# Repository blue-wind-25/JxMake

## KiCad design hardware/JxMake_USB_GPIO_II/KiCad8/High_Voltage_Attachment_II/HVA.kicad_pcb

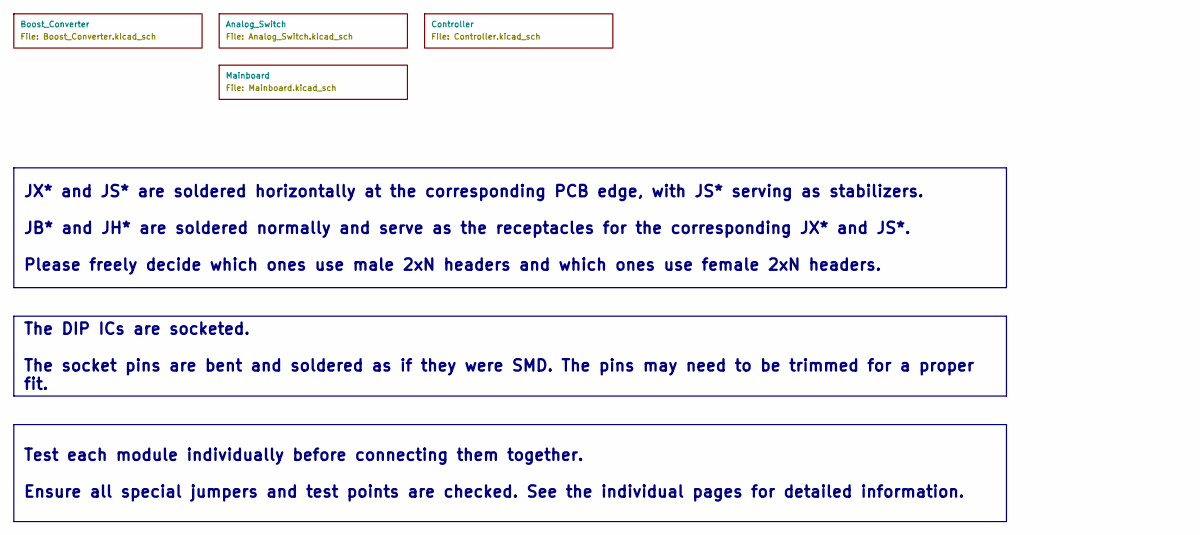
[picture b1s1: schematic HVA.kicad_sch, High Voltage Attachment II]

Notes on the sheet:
Test each module individually before connecting them together. Ensure all special jumpers and test points are checked. See the individual pages for detailed information.
The DIP ICs are socketed. The socket pins are bent and soldered as if they were SMD. The pins may need to be trimmed for a proper fit.
JX* and JS* are soldered horizontally at the corresponding PCB edge, with JS* serving as stabilizers. JB* and JH* are soldered normally and serve as the receptacles for the corresponding JX* and JS*. Please freely decide which ones use male 2xN headers and which ones use female 2xN headers.

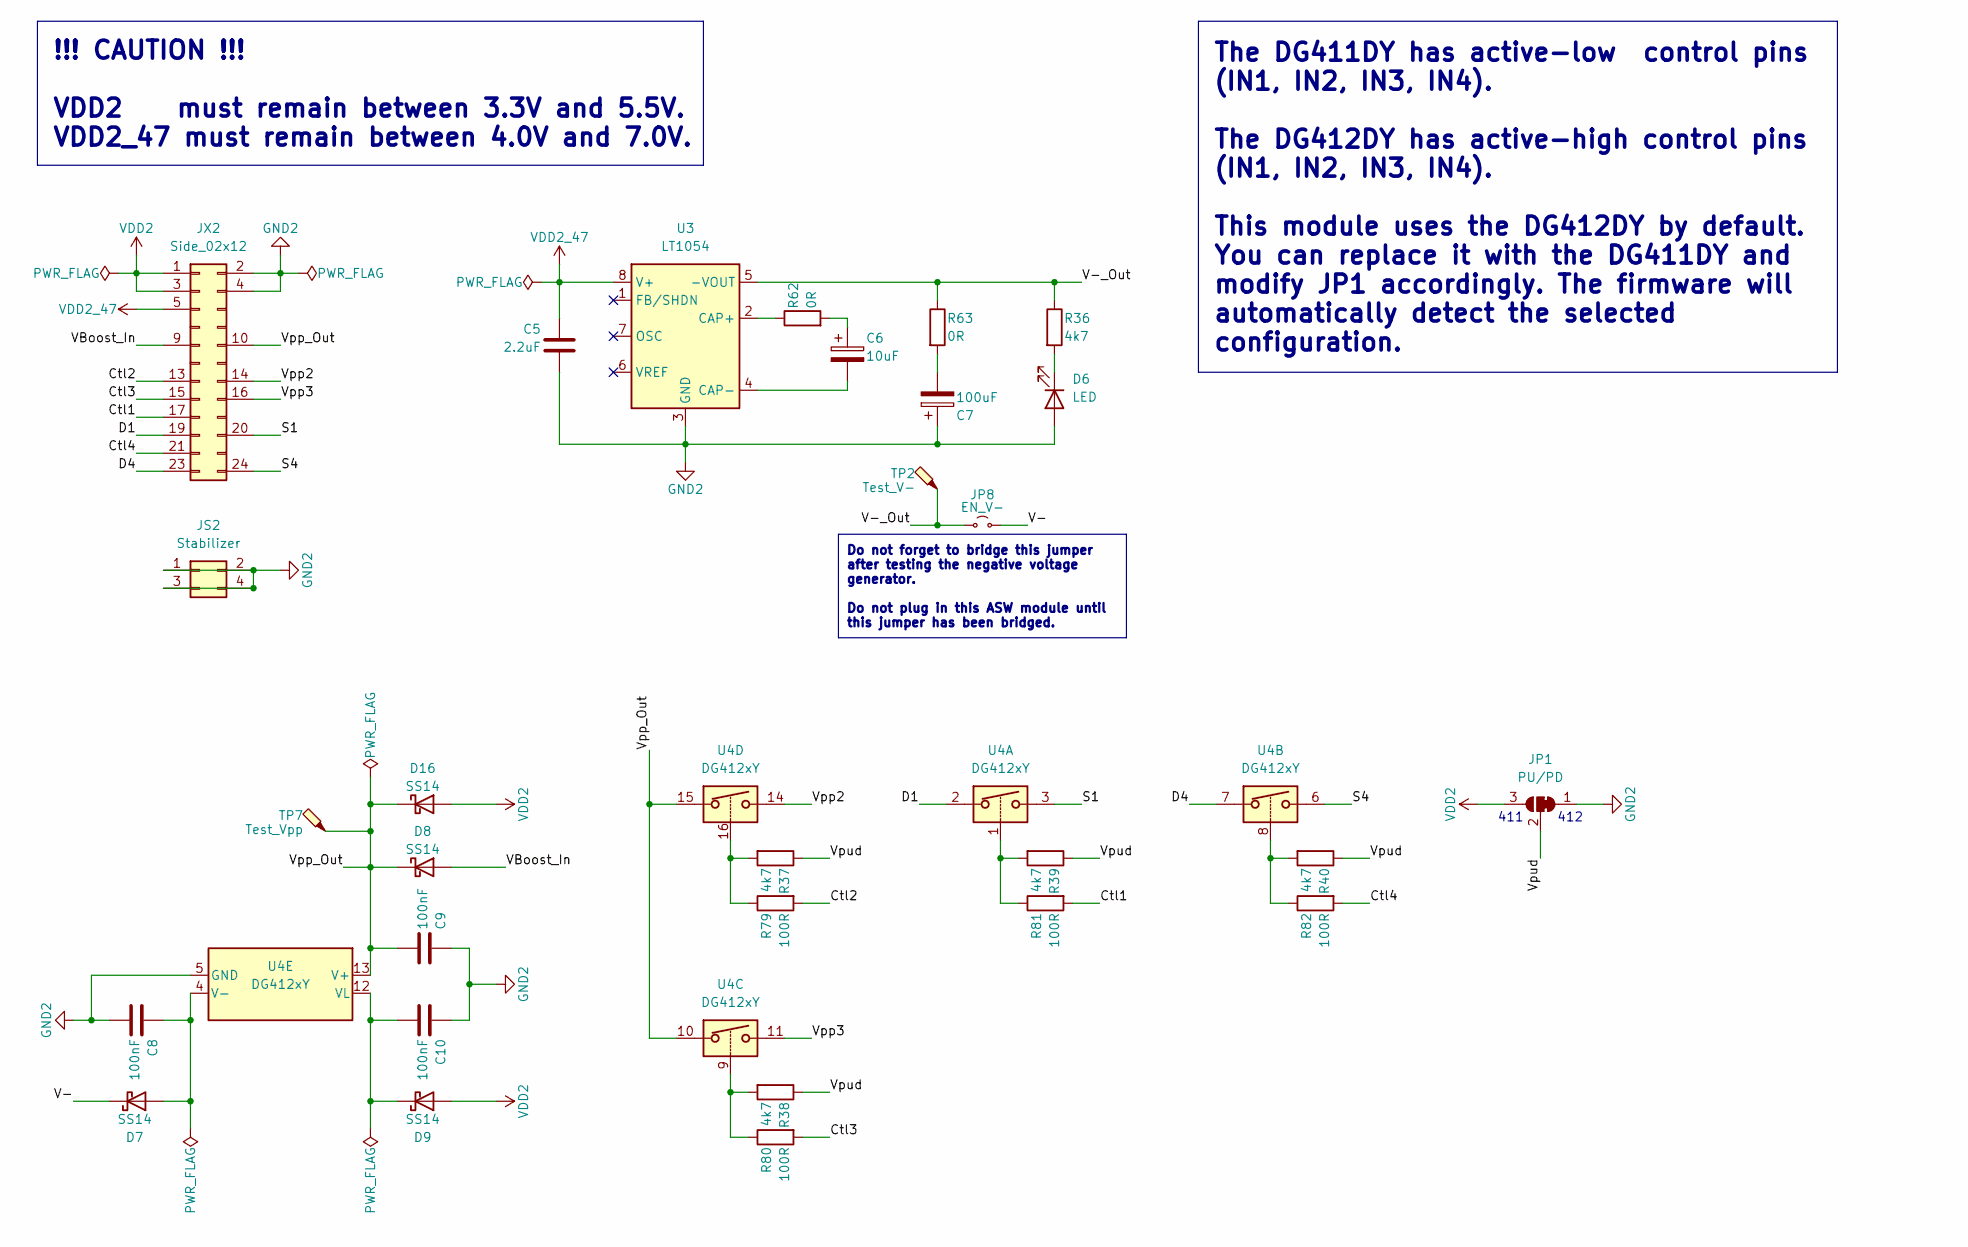
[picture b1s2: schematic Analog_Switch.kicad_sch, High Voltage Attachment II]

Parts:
C5: 2.2uF; C_0805_2012Metric_Pad1.18x1.45mm_HandSolder
C6: 10uF; CP_EIA-7360-38_Kemet-E_Pad2.25x4.25mm_HandSolder
C7: 100uF; CP_EIA-7360-38_Kemet-E_Pad2.25x4.25mm_HandSolder
C8, C9, C10: 100nF; C_0805_2012Metric_Pad1.18x1.45mm_HandSolder
D6: LED; LED_0805_2012Metric_Pad1.15x1.40mm_HandSolder
D7, D8, D9, D16: SS14; D_SMA
JP1: PU/PD; SolderJumper-3_P1.3mm_Bridged12_RoundedPad1.0x1.5mm
JP8: EN_V-; SolderJumper-2_P1.3mm_Open_RoundedPad1.0x1.5mm
JS2: Stabilizer; PinHeader_2x02_P2.54mm_Vertical
JX2: Side_02x12; PinHeader_2x12_P2.54mm_Vertical
R36, R37, R38, R39, R40: 4k7; R_0805_2012Metric_Pad1.20x1.40mm_HandSolder
R62, R63: 0R; R_0805_2012Metric_Pad1.20x1.40mm_HandSolder
R79, R80, R81, R82: 100R; R_0805_2012Metric_Pad1.20x1.40mm_HandSolder
TP2: Test_V-; TestPoint_THTPad_D1.5mm_Drill0.7mm
TP7: Test_Vpp; TestPoint_THTPad_D1.5mm_Drill0.7mm
U3: LT1054; DIP-8_W7.62mm_LongPads
U4: DG412xY; SOIC-16_3.9x9.9mm_P1.27mm

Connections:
/Analog_Switch/Ctl1: JX2.17, R81.2
/Analog_Switch/Ctl2: JX2.13, R79.2
/Analog_Switch/Ctl3: JX2.15, R80.2
/Analog_Switch/Ctl4: JX2.21, R82.2
/Analog_Switch/D1: JX2.19, U4.2
/Analog_Switch/D4: JX2.23, U4.7
/Analog_Switch/S1: JX2.20, U4.3
/Analog_Switch/S4: JX2.24, U4.6
/Analog_Switch/V-: D7.1 (K), JP8.2 (B)
/Analog_Switch/V-_Out: JP8.1 (A), R36.1, R63.1, TP2.1, U3.5 (-VOUT)
/Analog_Switch/VBoost_In: D8.2 (A), JX2.9
/Analog_Switch/Vpp2: JX2.14, U4.14
/Analog_Switch/Vpp3: JX2.16, U4.11
/Analog_Switch/Vpp_Out: C9.2, D8.1 (K), D16.1 (K), JX2.10, TP7.1, U4.10, U4.13 (V+), U4.15
/Analog_Switch/Vpud: JP1.2 (C), R37.1, R38.1, R39.1, R40.1
GND2: C5.2, C7.1, C8.2, C9.1, C10.1, D6.2 (A), JP1.1 (A), JS2.1, JS2.2, JS2.3, JS2.4, JX2.2, JX2.4, U3.3 (GND), U4.5 (GND)
unnamed: C6.1, R62.2
unnamed: C7.2, R63.2
unnamed: D6.1 (K), R36.2
unnamed: C8.1, D7.2 (A), U4.4 (V-)
unnamed: C10.2, D9.1 (K), U4.12 (VL)
unnamed: R37.2, R79.1, U4.16
unnamed: R38.2, R80.1, U4.9
unnamed: R39.2, R81.1, U4.1
unnamed: R40.2, R82.1, U4.8
unnamed: R62.1, U3.2 (CAP+)
unnamed: C6.2, U3.4 (CAP-)
VDD2: D9.2 (A), D16.2 (A), JP1.3 (B), JX2.1, JX2.3
VDD2_47: C5.1, JX2.5, U3.8 (V+)

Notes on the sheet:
Do not forget to bridge this jumper after testing the negative voltage generator. Do not plug in this ASW module until this jumper has been bridged.
The DG411DY has active-low control pins (IN1, IN2, IN3, IN4). The DG412DY has active-high control pins (IN1, IN2, IN3, IN4). This module uses the DG412DY by default. You can replace it with the DG411DY and modify JP1 accordingly. The firmware will automatically detect the selected configuration.
!!! CAUTION !!! VDD2 must remain between 3.3V and 5.5V. VDD2_47 must remain between 4.0V and 7.0V.
411
412

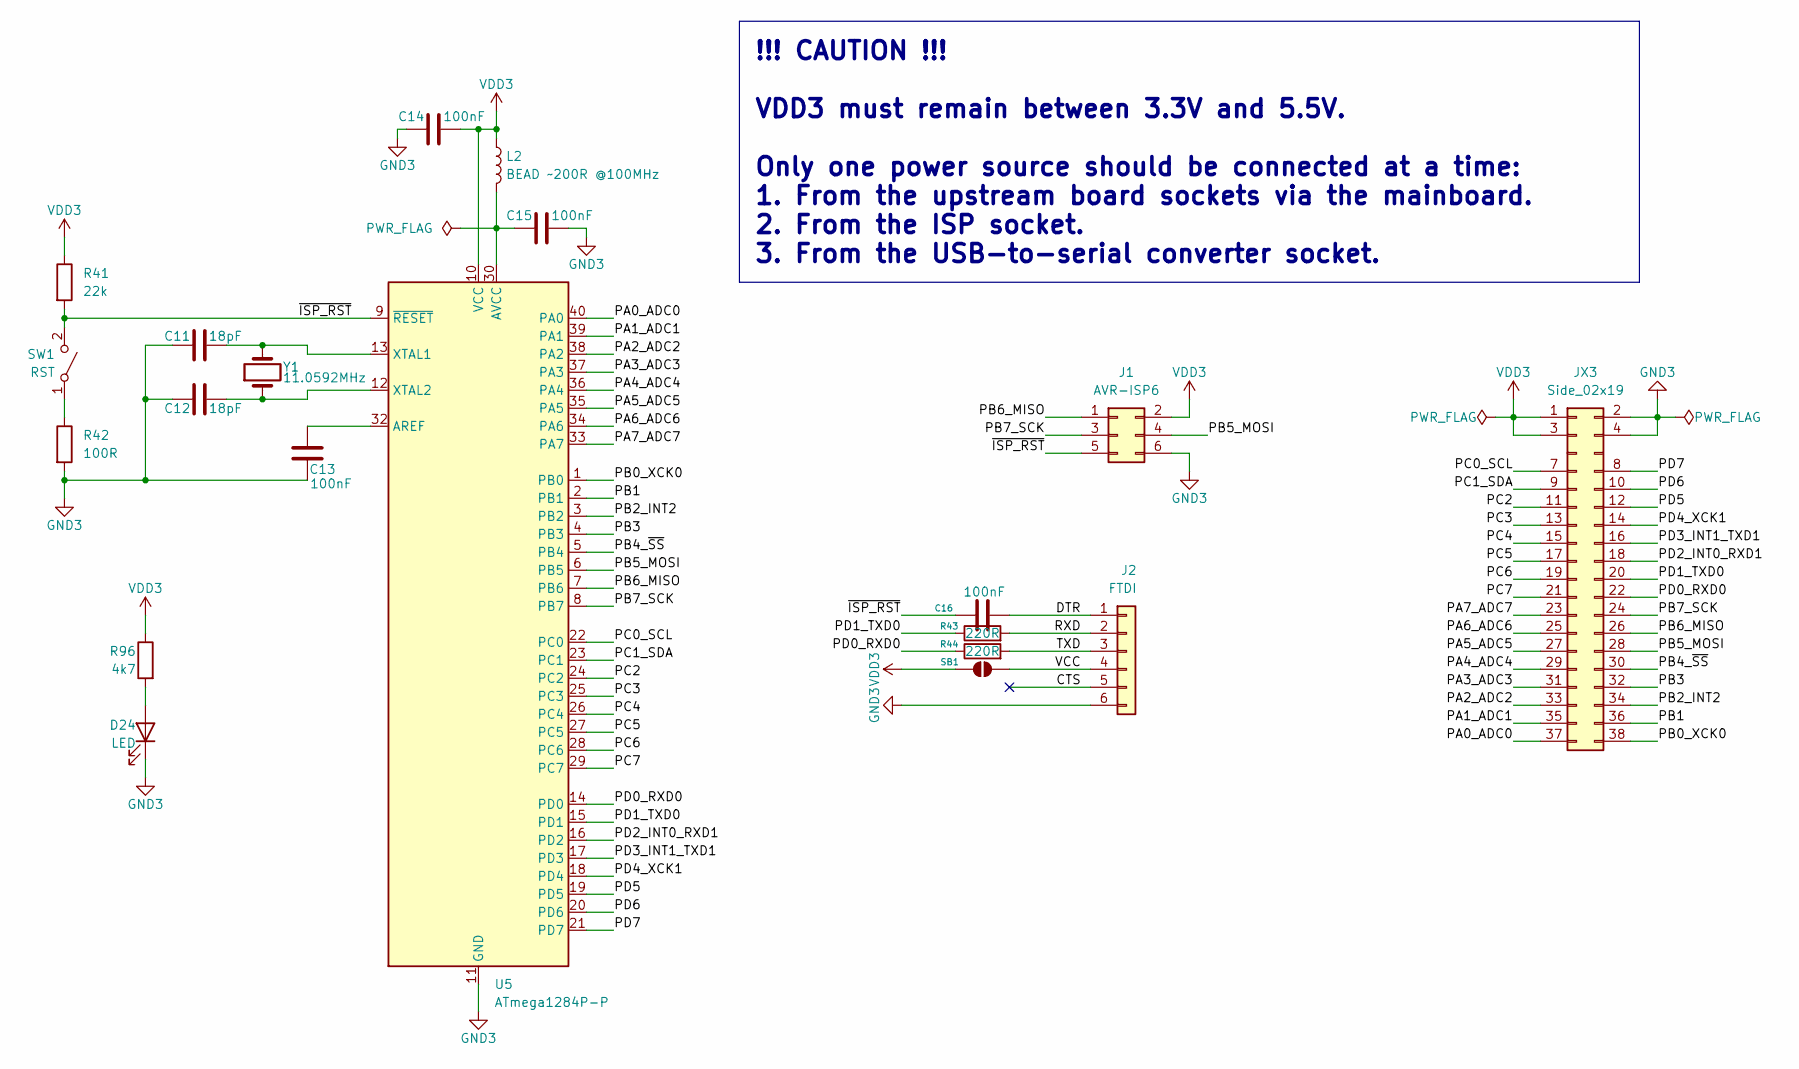
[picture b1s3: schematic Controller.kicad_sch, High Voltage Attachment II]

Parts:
C11, C12: 18pF; C_0805_2012Metric_Pad1.18x1.45mm_HandSolder
C13, C14, C15, C16: 100nF; C_0805_2012Metric_Pad1.18x1.45mm_HandSolder
D24: LED; LED_0805_2012Metric_Pad1.15x1.40mm_HandSolder
J1: AVR-ISP6; IDC-Header_2x03_P2.54mm_Horizontal
J2: FTDI; PinSocket_1x06_P2.54mm_Horizontal
JX3: Side_02x19; PinHeader_2x19_P2.54mm_Vertical
L2: BEAD ~200R @100MHz; L_0805_2012Metric_Pad1.15x1.40mm_HandSolder
R41: 22k; R_0805_2012Metric_Pad1.20x1.40mm_HandSolder
R42: 100R; R_0805_2012Metric_Pad1.20x1.40mm_HandSolder
R43, R44: 220R; R_0805_2012Metric_Pad1.20x1.40mm_HandSolder
R96: 4k7; R_0805_2012Metric_Pad1.20x1.40mm_HandSolder
SB1: Jumper_2_Small_Bridged; SolderJumper-2_P1.3mm_Open_RoundedPad1.0x1.5mm
SW1: RST; SW_SPST_FSMSM
U5: ATmega1284P-P; DIP-40_W15.24mm
Y1: 11.0592MHz; Crystal_SMD_HC49-SD

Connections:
/Controller/CTS: J2.5
/Controller/DTR: C16.2, J2.1
/Controller/PA0_ADC0: JX3.37, U5.40 (PA0)
/Controller/PA1_ADC1: JX3.35, U5.39 (PA1)
/Controller/PA2_ADC2: JX3.33, U5.38 (PA2)
/Controller/PA3_ADC3: JX3.31, U5.37 (PA3)
/Controller/PA4_ADC4: JX3.29, U5.36 (PA4)
/Controller/PA5_ADC5: JX3.27, U5.35 (PA5)
/Controller/PA6_ADC6: JX3.25, U5.34 (PA6)
/Controller/PA7_ADC7: JX3.23, U5.33 (PA7)
/Controller/PB0_XCK0: JX3.38, U5.1 (PB0)
/Controller/PB1: JX3.36, U5.2 (PB1)
/Controller/PB2_INT2: JX3.34, U5.3 (PB2)
/Controller/PB3: JX3.32, U5.4 (PB3)
/Controller/PB4_~SS: JX3.30, U5.5 (PB4)
/Controller/PB5_MOSI: J1.4, JX3.28, U5.6 (PB5)
/Controller/PB6_MISO: J1.1, JX3.26, U5.7 (PB6)
/Controller/PB7_SCK: J1.3, JX3.24, U5.8 (PB7)
/Controller/PC0_SCL: JX3.7, U5.22 (PC0)
/Controller/PC1_SDA: JX3.9, U5.23 (PC1)
/Controller/PC2: JX3.11, U5.24 (PC2)
/Controller/PC3: JX3.13, U5.25 (PC3)
/Controller/PC4: JX3.15, U5.26 (PC4)
/Controller/PC5: JX3.17, U5.27 (PC5)
/Controller/PC6: JX3.19, U5.28 (PC6)
/Controller/PC7: JX3.21, U5.29 (PC7)
/Controller/PD0_RXD0: JX3.22, R44.1, U5.14 (PD0)
/Controller/PD1_TXD0: JX3.20, R43.1, U5.15 (PD1)
/Controller/PD2_INT0_RXD1: JX3.18, U5.16 (PD2)
/Controller/PD3_INT1_TXD1: JX3.16, U5.17 (PD3)
/Controller/PD4_XCK1: JX3.14, U5.18 (PD4)
/Controller/PD5: JX3.12, U5.19 (PD5)
/Controller/PD6: JX3.10, U5.20 (PD6)
/Controller/PD7: JX3.8, U5.21 (PD7)
/Controller/RXD: J2.2, R43.2
/Controller/TXD: J2.3, R44.2
/Controller/VCC: J2.4, SB1.2 (B)
/Controller/~ISP_RST: C16.1, J1.5, R41.2, SW1.2 (B), U5.9 (~RESET)
GND3: C11.1, C12.1, C13.1, C14.1, C15.2, D24.1 (K), J1.6, J2.6, JX3.2, JX3.4, R42.2, U5.11 (GND), U5.31 (GND)
unnamed: D24.2 (A), R96.2
unnamed: R42.1, SW1.1 (A)
unnamed: C13.2, U5.32 (AREF)
unnamed: C15.1, L2.2, U5.30 (AVCC)
unnamed: C11.2, U5.13 (XTAL1), Y1.2
unnamed: C12.2, U5.12 (XTAL2), Y1.1
VDD3: C14.2, J1.2, JX3.1, JX3.3, L2.1, R41.1, R96.1, SB1.1 (A), U5.10 (VCC)

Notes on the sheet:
!!! CAUTION !!! VDD3 must remain between 3.3V and 5.5V. Only one power source should be connected at a time: 1. From the upstream board sockets via the mainboard. 2. From the ISP socket. 3. From the USB-to-serial converter socket.

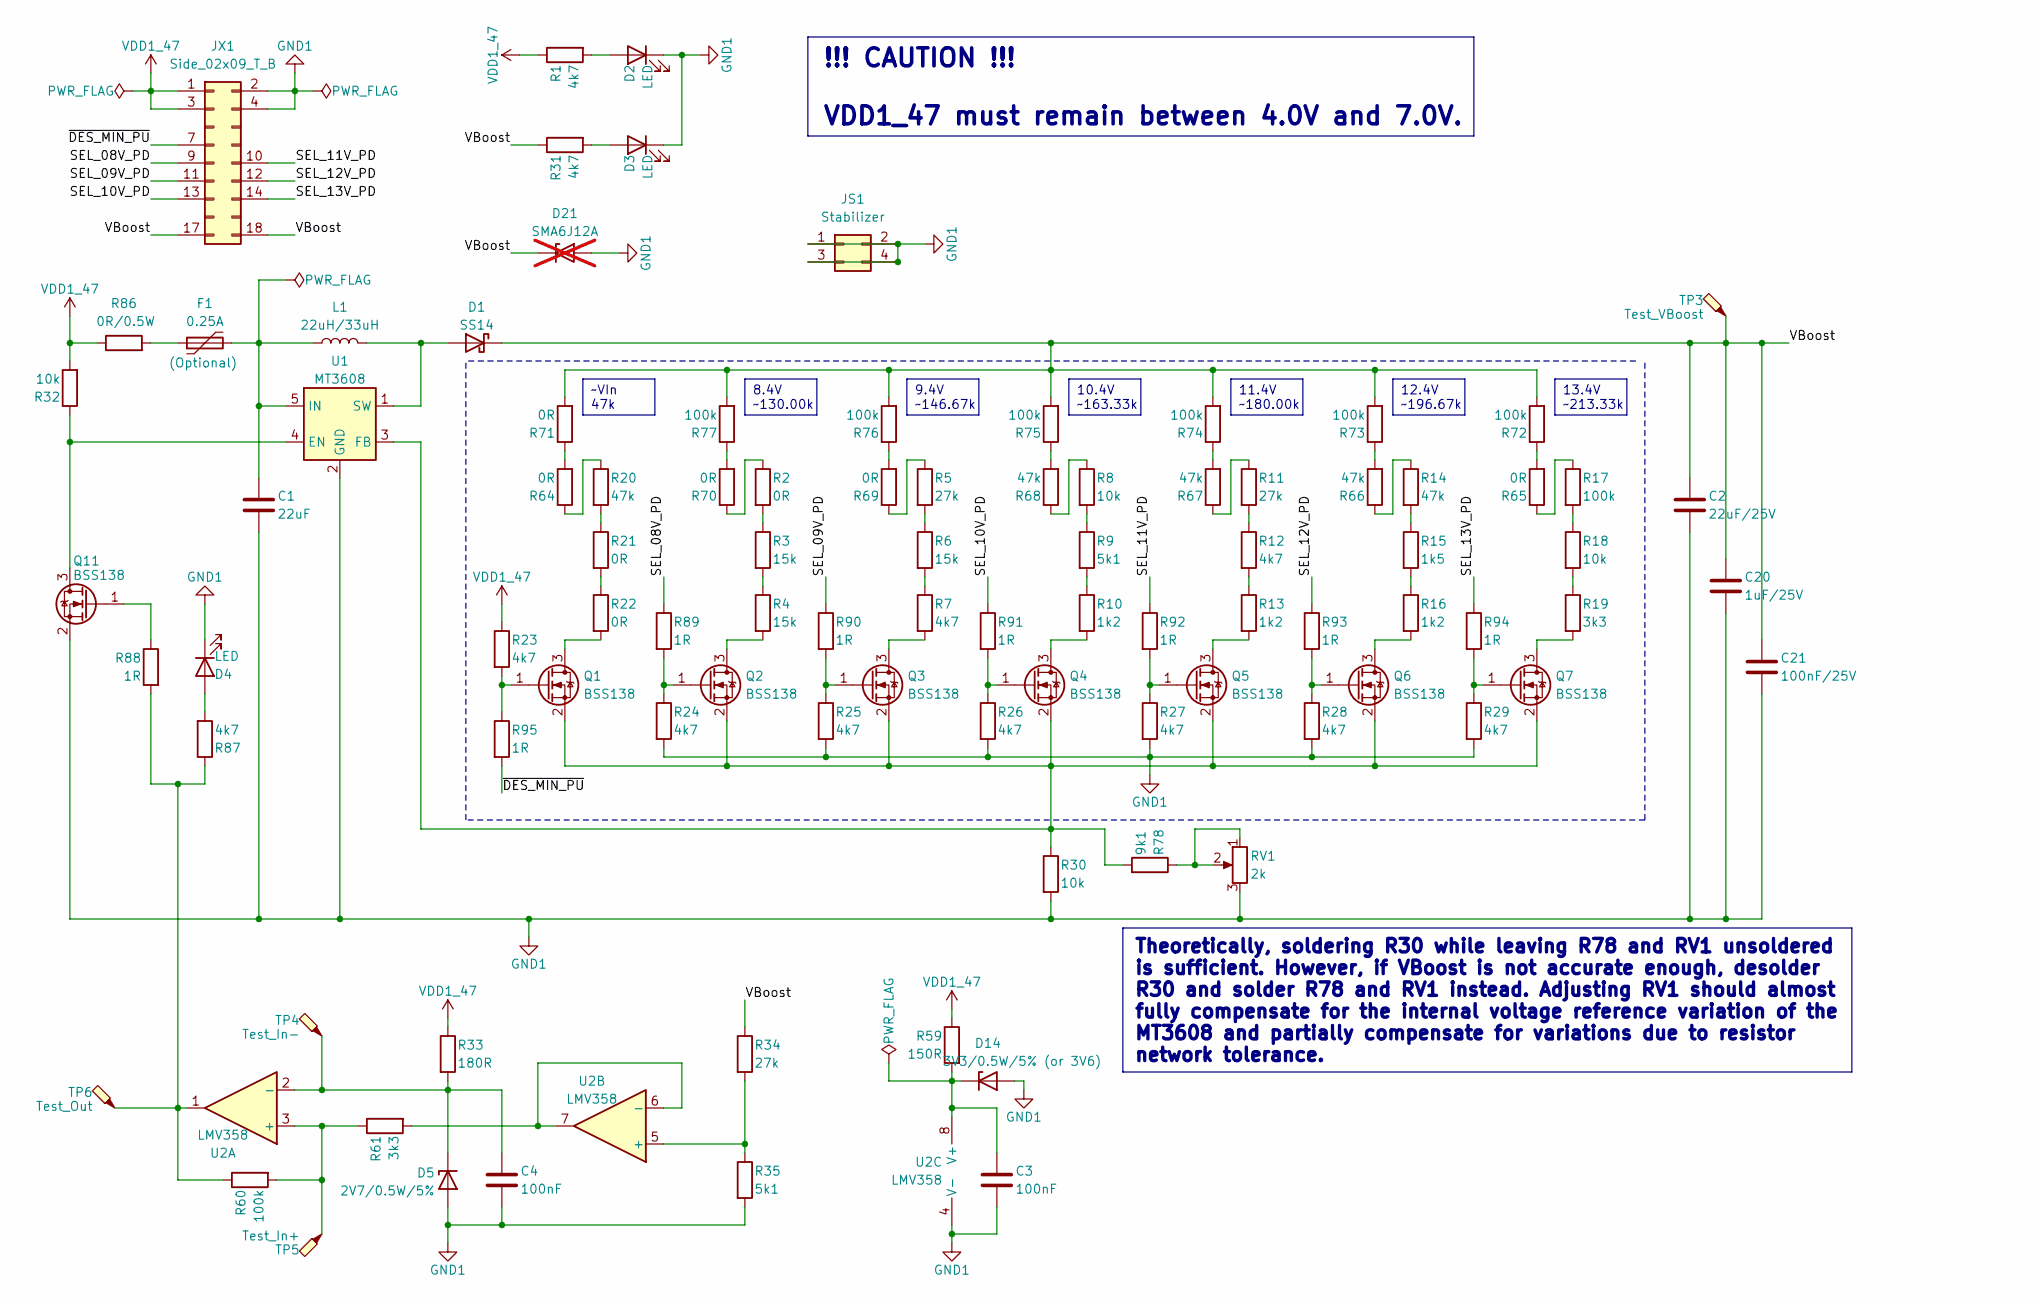
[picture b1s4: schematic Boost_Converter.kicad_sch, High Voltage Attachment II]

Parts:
C1: 22uF; C_1206_3216Metric_Pad1.33x1.80mm_HandSolder
C2: 22uF/25V; C_1206_3216Metric_Pad1.33x1.80mm_HandSolder
C3, C4: 100nF; C_0805_2012Metric_Pad1.18x1.45mm_HandSolder
C20: 1uF/25V; C_0805_2012Metric_Pad1.18x1.45mm_HandSolder
C21: 100nF/25V; C_0805_2012Metric_Pad1.18x1.45mm_HandSolder
D1: SS14; D_SMA
D2, D3, D4: LED; LED_0805_2012Metric_Pad1.15x1.40mm_HandSolder
D5: 2V7/0.5W/5%; D_MELF_Handsoldering
D14: 3V3/0.5W/5% (or 3V6); D_MELF_Handsoldering
D21: SMA6J12A; D_SMA; not fitted
F1: 0.25A; R_1206_3216Metric_Pad1.30x1.75mm_HandSolder
JS1: Stabilizer; PinHeader_2x02_P2.54mm_Vertical
JX1: Side_02x09_T_B; PinHeader_2x09_P2.54mm_Vertical
L1: 22uH/33uH; L_12x12mm_H8mm
Q1, Q2, Q3, Q4, Q5, Q6, Q7, Q11: BSS138; SOT-23_Handsoldering
R1, R7, R12, R23, R24, R25, R26, R27, R28, R29, R31, R87: 4k7; R_0805_2012Metric_Pad1.20x1.40mm_HandSolder
R2, R21, R22, R64, R65, R69, R70, R71: 0R; R_0805_2012Metric_Pad1.20x1.40mm_HandSolder
R3, R4, R6: 15k; R_0805_2012Metric_Pad1.20x1.40mm_HandSolder
R5, R11, R34: 27k; R_0805_2012Metric_Pad1.20x1.40mm_HandSolder
R8, R18, R30, R32: 10k; R_0805_2012Metric_Pad1.20x1.40mm_HandSolder
R9, R35: 5k1; R_0805_2012Metric_Pad1.20x1.40mm_HandSolder
R10, R13, R16: 1k2; R_0805_2012Metric_Pad1.20x1.40mm_HandSolder
R14, R20, R66, R67, R68: 47k; R_0805_2012Metric_Pad1.20x1.40mm_HandSolder
R15: 1k5; R_0805_2012Metric_Pad1.20x1.40mm_HandSolder
R17, R60, R72, R73, R74, R75, R76, R77: 100k; R_0805_2012Metric_Pad1.20x1.40mm_HandSolder
R19, R61: 3k3; R_0805_2012Metric_Pad1.20x1.40mm_HandSolder
R33: 180R; R_0805_2012Metric_Pad1.20x1.40mm_HandSolder
R59: 150R; R_0805_2012Metric_Pad1.20x1.40mm_HandSolder
R78: 9k1; R_0805_2012Metric_Pad1.20x1.40mm_HandSolder
R86: 0R/0.5W; R_1210_3225Metric_Pad1.30x2.65mm_HandSolder
R88, R89, R90, R91, R92, R93, R94, R95: 1R; R_0805_2012Metric_Pad1.20x1.40mm_HandSolder
RV1: 2k; Potentiometer_Bourns_3296W_Vertical
TP3: Test_VBoost; TestPoint_THTPad_D1.5mm_Drill0.7mm
TP4: Test_In-; TestPoint_THTPad_D1.5mm_Drill0.7mm
TP5: Test_In+; TestPoint_THTPad_D1.5mm_Drill0.7mm
TP6: Test_Out; TestPoint_THTPad_D1.5mm_Drill0.7mm
U1: MT3608; SOT-23-6
U2: LMV358; SOIC-8_3.9x4.9mm_P1.27mm

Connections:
/Boost_Converter/SEL_08V_PD: JX1.9, R89.1
/Boost_Converter/SEL_09V_PD: JX1.11, R90.1
/Boost_Converter/SEL_10V_PD: JX1.13, R91.1
/Boost_Converter/SEL_11V_PD: JX1.10, R92.1
/Boost_Converter/SEL_12V_PD: JX1.12, R93.1
/Boost_Converter/SEL_13V_PD: JX1.14, R94.1
/Boost_Converter/VBoost: C2.1, C20.1, C21.1, D1.1 (K), D21.1 (A1), JX1.17, JX1.18, R31.1, R34.1, R71.2, R72.2, R73.2, R74.2, R75.2, R76.2, R77.2, TP3.1
/Boost_Converter/~DES_MIN_PU: JX1.7, R95.2
GND1: C1.2, C2.2, C3.2, C4.2, C20.2, C21.2, D2.1 (K), D3.1 (K), D4.1 (K), D5.2 (A), D14.2 (A), D21.2 (A2), JS1.1, JS1.2, JS1.3, JS1.4, JX1.2, JX1.4, Q11.2 (S), R24.2, R25.2, R26.2, R27.2, R28.2, R29.2, R30.2, R35.2, RV1.3, U1.2 (GND), U2.4 (V-)
unnamed: D1.2 (A), L1.2, U1.1 (SW)
unnamed: D2.2 (A), R1.2
unnamed: D3.2 (A), R31.2
unnamed: D4.2 (A), R87.2
unnamed: C4.1, D5.1 (K), R33.2, TP4.1, U2.2 (-)
unnamed: C3.1, D14.1 (K), R59.2, U2.8 (V+)
unnamed: F1.1, R86.2
unnamed: Q1.3 (D), R22.2
unnamed: Q1.1 (G), R23.2, R95.1
unnamed: Q1.2 (S), Q2.2 (S), Q3.2 (S), Q4.2 (S), Q5.2 (S), Q6.2 (S), Q7.2 (S), R30.1, R78.2, U1.3 (FB)
unnamed: Q2.3 (D), R4.2
unnamed: Q2.1 (G), R24.1, R89.2
unnamed: Q3.3 (D), R7.2
unnamed: Q3.1 (G), R25.1, R90.2
unnamed: Q4.3 (D), R10.2
unnamed: Q4.1 (G), R26.1, R91.2
unnamed: Q5.3 (D), R13.2
unnamed: Q5.1 (G), R27.1, R92.2
unnamed: Q6.3 (D), R16.2
unnamed: Q6.1 (G), R28.1, R93.2
unnamed: Q7.3 (D), R19.2
unnamed: Q7.1 (G), R29.1, R94.2
unnamed: Q11.3 (D), R32.1, U1.4 (EN)
unnamed: Q11.1 (G), R88.1
unnamed: R2.1, R70.1
unnamed: R2.2, R3.1
unnamed: R3.2, R4.1
unnamed: R5.1, R69.1
unnamed: R5.2, R6.1
unnamed: R6.2, R7.1
unnamed: R8.2, R9.1
unnamed: R9.2, R10.1
unnamed: R11.1, R67.1
unnamed: R11.2, R12.1
unnamed: R12.2, R13.1
unnamed: R14.1, R66.1
unnamed: R14.2, R15.1
unnamed: R15.2, R16.1
unnamed: R17.1, R65.1
unnamed: R17.2, R18.1
unnamed: R18.2, R19.1
unnamed: R20.1, R64.1
unnamed: R20.2, R21.1
unnamed: R21.2, R22.1
unnamed: R60.1, R87.1, R88.2, TP6.1, U2.1
unnamed: R64.2, R71.1
unnamed: R65.2, R72.1
unnamed: R66.2, R73.1
unnamed: R67.2, R74.1
unnamed: R8.1, R68.1
unnamed: R68.2, R75.1
unnamed: R69.2, R76.1
unnamed: R70.2, R77.1
unnamed: R78.1, RV1.1, RV1.2
unnamed: C1.1, F1.2, L1.1, U1.5 (IN)
unnamed: R60.2, R61.1, TP5.1, U2.3 (+)
unnamed: R34.2, R35.1, U2.5 (+)
unnamed: R61.2, U2.6 (-), U2.7
VDD1_47: JX1.1, JX1.3, R1.1, R23.1, R32.2, R33.1, R59.1, R86.1

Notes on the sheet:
10.4V ~163.33k
!!! CAUTION !!! VDD1_47 must remain between 4.0V and 7.0V.
13.4V ~213.33k
9.4V ~146.67k
Theoretically, soldering R30 while leaving R78 and RV1 unsoldered is sufficient. However, if VBoost is not accurate enough, desolder R30 and solder R78 and RV1 instead. Adjusting RV1 should almost fully compensate for the internal voltage reference variation of the MT3608 and partially compensate f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
8.4V ~130.00k
12.4V ~196.67k
~VIn 47k
11.4V ~180.00k

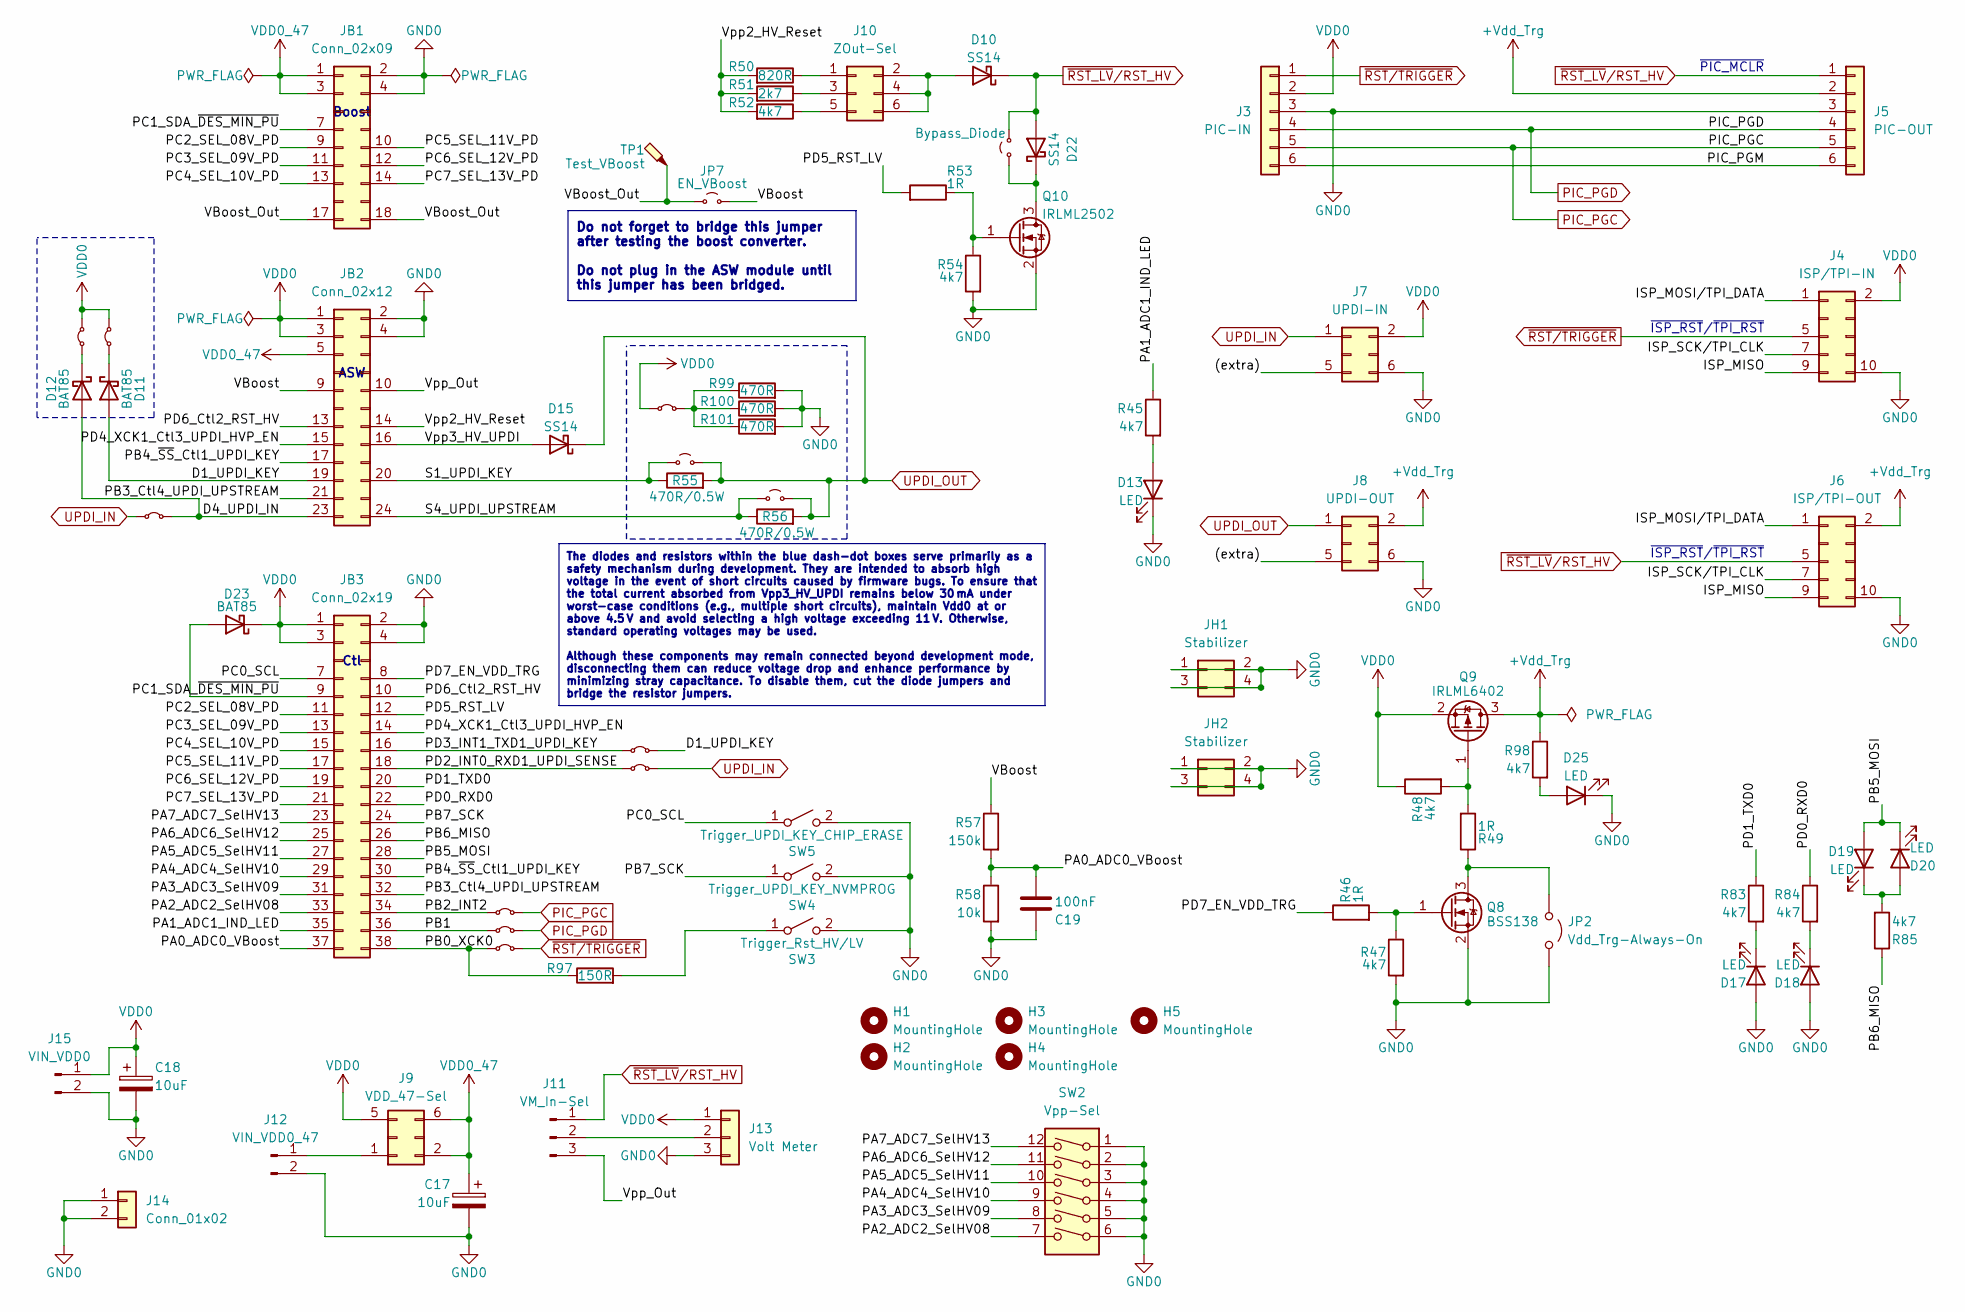
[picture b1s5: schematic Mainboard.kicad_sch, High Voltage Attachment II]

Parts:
C17, C18: 10uF; CP_EIA-3528-21_Kemet-B_Pad1.50x2.35mm_HandSolder
C19: 100nF; C_0805_2012Metric_Pad1.18x1.45mm_HandSolder
D10, D15, D22: SS14; D_SMA
D11, D12, D23: BAT85; D_SMA
D13, D17, D18, D19, D20, D25: LED; LED_0805_2012Metric_Pad1.15x1.40mm_HandSolder
H1, H2, H3, H4, H5: MountingHole; MountingHole_3.2mm_M3
J3: PIC-IN; PinHeader_1x06_P2.54mm_Horizontal
J4: ISP/TPI-IN; IDC-Header_2x05_P2.54mm_Vertical
J5: PIC-OUT; PinSocket_1x06_P2.54mm_Horizontal
J6: ISP/TPI-OUT; IDC-Header_2x05_P2.54mm_Vertical
J7: UPDI-IN; IDC-Header_2x03_P2.54mm_Vertical
J8: UPDI-OUT; IDC-Header_2x03_P2.54mm_Vertical
J9: VDD_47-Sel; PinHeader_2x03_P2.54mm_Vertical
J10: ZOut-Sel; PinHeader_2x03_P2.54mm_Vertical
J11: VM_In-Sel; PinHeader_1x03_P2.54mm_Vertical
J12: VIN_VDD0_47; Molex_KK-254_AE-6410-02A_1x02_P2.54mm_Vertical
J13: Volt Meter; FanPinHeader_1x03_P2.54mm_Vertical
J14: Conn_01x02; PinHeader_1x02_P2.54mm_Vertical
J15: VIN_VDD0; Molex_KK-254_AE-6410-02A_1x02_P2.54mm_Vertical
JB1: Conn_02x09; PinHeader_2x09_P2.54mm_Vertical
JB2: Conn_02x12; PinHeader_2x12_P2.54mm_Vertical
JB3: Conn_02x19; PinHeader_2x19_P2.54mm_Vertical
JH1, JH2: Stabilizer; PinHeader_2x02_P2.54mm_Vertical
JP2: Vdd_Trg-Always-On; PinHeader_2x01_P2.54mm_Vertical
JP3, JP4, JP5, JP6, JP10, JP11: Jumper_2_Small_Bridged; SolderJumper-2_P1.3mm_Bridged_Pad1.0x1.5mm
JP7: EN_VBoost; SolderJumper-2_P1.3mm_Open_RoundedPad1.0x1.5mm
JP9: Bypass_Diode; SolderJumper-2_P1.3mm_Open_RoundedPad1.0x1.5mm
JP12, JP13: Jumper_2_Small_Open; SolderJumper-2_P1.3mm_Open_RoundedPad1.0x1.5mm
JP14, JP15, JP16: Jumper_2_Small_Bridged; SolderJumper-2_P1.3mm_Bridged_RoundedPad1.0x1.5mm
Q8: BSS138; SOT-23_Handsoldering
Q9: IRLML6402; SOT-23_Handsoldering
Q10: IRLML2502; SOT-23_Handsoldering
R45, R47, R48, R52, R54, R83, R84, R85, R98: 4k7; R_0805_2012Metric_Pad1.20x1.40mm_HandSolder
R46, R49, R53: 1R; R_0805_2012Metric_Pad1.20x1.40mm_HandSolder
R50: 820R; R_0805_2012Metric_Pad1.20x1.40mm_HandSolder
R51: 2k7; R_0805_2012Metric_Pad1.20x1.40mm_HandSolder
R55, R56: 470R/0.5W; R_2010_5025Metric_Pad1.40x2.65mm_HandSolder
R57: 150k; R_0805_2012Metric_Pad1.20x1.40mm_HandSolder
R58: 10k; R_0805_2012Metric_Pad1.20x1.40mm_HandSolder
R97: 150R; R_0805_2012Metric_Pad1.20x1.40mm_HandSolder
R99, R100, R101: 470R; R_0805_2012Metric_Pad1.20x1.40mm_HandSolder
SW2: Vpp-Sel; SW_DIP_SPSTx06_Slide_9.78x17.42mm_W7.62mm_P2.54mm
SW3: Trigger_Rst_HV/LV; SW_SPST_FSMSM
SW4: Trigger_UPDI_KEY_NVMPROG; SW_SPST_FSMSM
SW5: Trigger_UPDI_KEY_CHIP_ERASE; SW_SPST_FSMSM
TP1: Test_VBoost; TestPoint_THTPad_D1.5mm_Drill0.7mm

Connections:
+Vdd_Trg: J5.2, J6.2, J8.2, Q9.3 (D), R98.1
/Mainboard/(extra): J7.5, J8.5
/Mainboard/D1_UPDI_KEY: D11.2 (A), JB2.19, JP10.2 (B)
/Mainboard/D4_UPDI_IN: D12.2 (A), JB2.23, JP6.2 (B)
/Mainboard/ISP_MISO: J4.9, J6.9
/Mainboard/ISP_MOSI/TPI_DATA: J4.1, J6.1
/Mainboard/ISP_SCK/TPI_CLK: J4.7, J6.7
/Mainboard/PA0_ADC0_VBoost: C19.2, JB3.37, R57.2, R58.1
/Mainboard/PA1_ADC1_IND_LED: JB3.35, R45.1
/Mainboard/PA2_ADC2_SelHV08: JB3.33, SW2.7
/Mainboard/PA3_ADC3_SelHV09: JB3.31, SW2.8
/Mainboard/PA4_ADC4_SelHV10: JB3.29, SW2.9
/Mainboard/PA5_ADC5_SelHV11: JB3.27, SW2.10
/Mainboard/PA6_ADC6_SelHV12: JB3.25, SW2.11
/Mainboard/PA7_ADC7_SelHV13: JB3.23, SW2.12
/Mainboard/PB0_XCK0: JB3.38, JP5.1 (A), R97.1
/Mainboard/PB1: JB3.36, JP4.1 (A)
/Mainboard/PB2_INT2: JB3.34, JP3.1 (A)
/Mainboard/PB3_Ctl4_UPDI_UPSTREAM: JB2.21, JB3.32
/Mainboard/PB4_~SS_Ctl1_UPDI_KEY: JB2.17, JB3.30
/Mainboard/PB5_MOSI: D19.2 (A), D20.1 (K), JB3.28
/Mainboard/PB6_MISO: JB3.26, R85.1
/Mainboard/PB7_SCK: JB3.24, SW4.1 (A)
/Mainboard/PC0_SCL: JB3.7, SW5.1 (A)
/Mainboard/PC1_SDA_~DES_MIN_PU: D23.2 (A), JB1.7, JB3.9
/Mainboard/PC2_SEL_08V_PD: JB1.9, JB3.11
/Mainboard/PC3_SEL_09V_PD: JB1.11, JB3.13
/Mainboard/PC4_SEL_10V_PD: JB1.13, JB3.15
/Mainboard/PC5_SEL_11V_PD: JB1.10, JB3.17
/Mainboard/PC6_SEL_12V_PD: JB1.12, JB3.19
/Mainboard/PC7_SEL_13V_PD: JB1.14, JB3.21
/Mainboard/PD0_RXD0: JB3.22, R84.1
/Mainboard/PD1_TXD0: JB3.20, R83.1
/Mainboard/PD2_INT0_RXD1_UPDI_SENSE: JB3.18, JP11.1 (A)
/Mainboard/PD3_INT1_TXD1_UPDI_KEY: JB3.16, JP10.1 (A)
/Mainboard/PD4_XCK1_Ctl3_UPDI_HVP_EN: JB2.15, JB3.14
/Mainboard/PD5_RST_LV: JB3.12, R53.2
/Mainboard/PD6_Ctl2_RST_HV: JB2.13, JB3.10
/Mainboard/PD7_EN_VDD_TRG: JB3.8, R46.1
/Mainboard/PIC_PGM: J3.6, J5.6
/Mainboard/S1_UPDI_KEY: JB2.20, JP13.1 (A), R55.1
/Mainboard/S4_UPDI_UPSTREAM: JB2.24, JP12.1 (A), R56.1
/Mainboard/VBoost: JB2.9, JP7.2 (B), R57.1
/Mainboard/VBoost_Out: JB1.17, JB1.18, JP7.1 (A), TP1.1
/Mainboard/Vpp2_HV_Reset: JB2.14, R50.2, R51.2, R52.2
/Mainboard/Vpp3_HV_UPDI: D15.2 (A), JB2.16
/Mainboard/Vpp_Out: J11.3, JB2.10
GND0: C17.2, C18.2, C19.1, D13.1 (K), D17.2 (A), D18.2 (A), D25.1 (K), J3.3, J4.10, J5.3, J6.10, J7.6, J8.6, J12.2, J13.3, J14.1, J14.2, J15.2, JB1.2, JB1.4, JB2.2, JB2.4, JB3.2, JB3.4, JH1.1, JH1.2, JH1.3, JH1.4, JH2.1, JH2.2, JH2.3, JH2.4, JP2.2 (B), Q8.2 (S), Q10.2 (S), R47.2, R54.2, R58.2, R99.2, R100.2, R101.2, SW2.1, SW2.2, SW2.3, SW2.4, SW2.5, SW2.6, SW3.2 (B), SW4.2 (B), SW5.2 (B)
unnamed: D10.2 (A), J10.2, J10.4, J10.6
unnamed: D11.1 (K), JP14.2 (B)
unnamed: D12.1 (K), JP15.2 (B)
unnamed: D13.2 (A), R45.2
unnamed: D17.1 (K), R83.2
unnamed: D18.1 (K), R84.2
unnamed: D19.1 (K), D20.2 (A), R85.2
unnamed: D22.1 (K), JP9.1 (A), Q10.3 (D)
unnamed: D25.2 (A), R98.2
unnamed: J10.1, R50.1
unnamed: J10.3, R51.1
unnamed: J10.5, R52.1
unnamed: J11.2, J13.2
unnamed: J9.1, J12.1
unnamed: JP2.1 (A), Q8.3 (D), R49.1
unnamed: JP16.2 (B), R99.1, R100.1, R101.1
unnamed: Q8.1 (G), R46.2, R47.1
unnamed: Q9.1 (G), R48.2, R49.2
unnamed: Q10.1 (G), R53.1, R54.1
unnamed: R97.2, SW3.1 (A)
PIC_PGC: J3.5, J5.5, JP3.2 (B)
PIC_PGD: J3.4, J5.4, JP4.2 (B)
UPDI_IN: J7.1, JP6.1 (A), JP11.2 (B)
UPDI_OUT: D15.1 (K), J8.1, JP12.2 (B), JP13.2 (B), R55.2, R56.2
VDD0: C18.1, D23.1 (K), J3.2, J4.2, J7.2, J9.5, J13.1, J15.1, JB2.1, JB2.3, JB3.1, JB3.3, JP14.1 (A), JP15.1 (A), JP16.1 (A), Q9.2 (S), R48.1
VDD0_47: C17.1, J9.2, J9.6, JB1.1, JB1.3, JB2.5
~RST_LV/RST_HV: D10.1 (K), D22.2 (A), J5.1, J6.5, J11.1, JP9.2 (B)
~RST/TRIGGER: J3.1, J4.5, JP5.2 (B)

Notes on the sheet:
Do not forget to bridge this jumper after testing the boost converter. Do not plug in the ASW module until this jumper has been bridged.
The diodes and resistors within the blue dash-dot boxes serve primarily as a safety mechanism during development. They are intended to absorb high voltage in the event of short circuits caused by firmware bugs. To ensure that the total current absorbed from Vpp3_HV_UPDI remains below 30 mA under wo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
Boost
~{ISP_RST}/~{TPI_RST}
ASW
~{PIC_MCLR}
Ctl

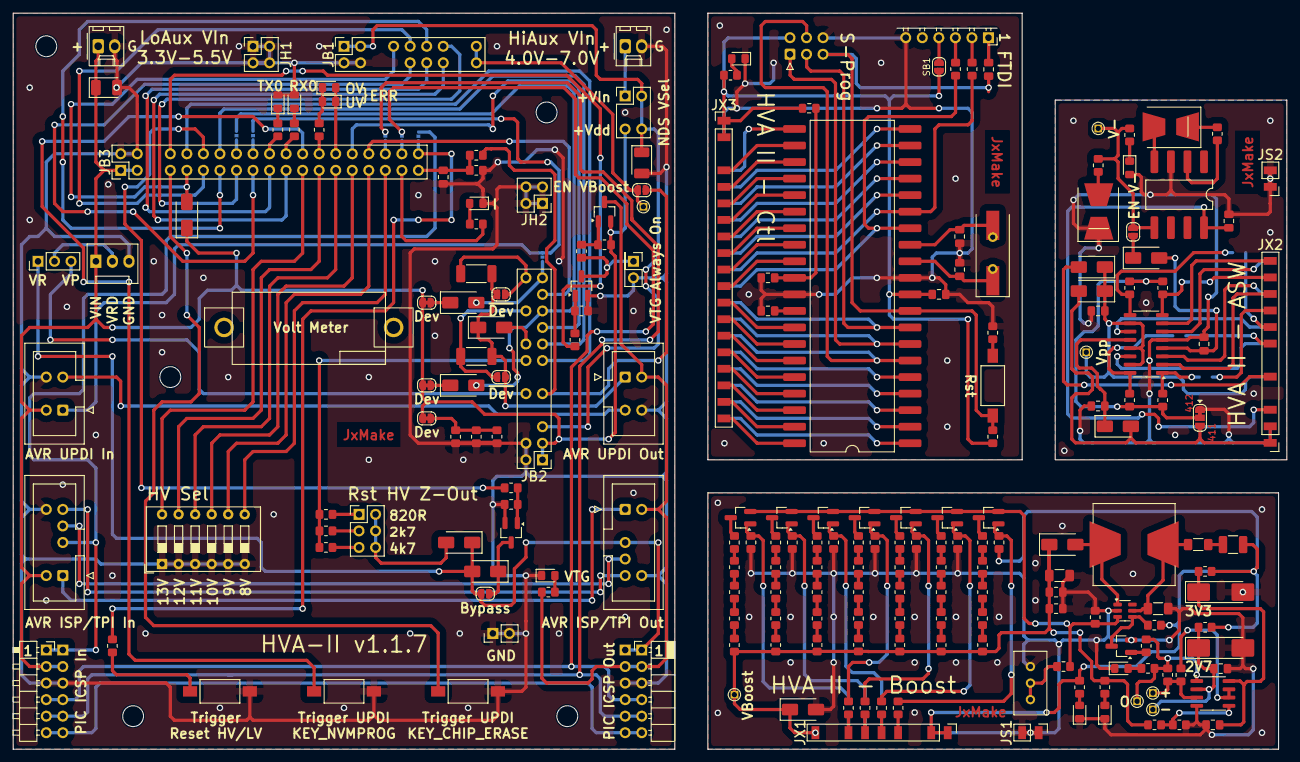
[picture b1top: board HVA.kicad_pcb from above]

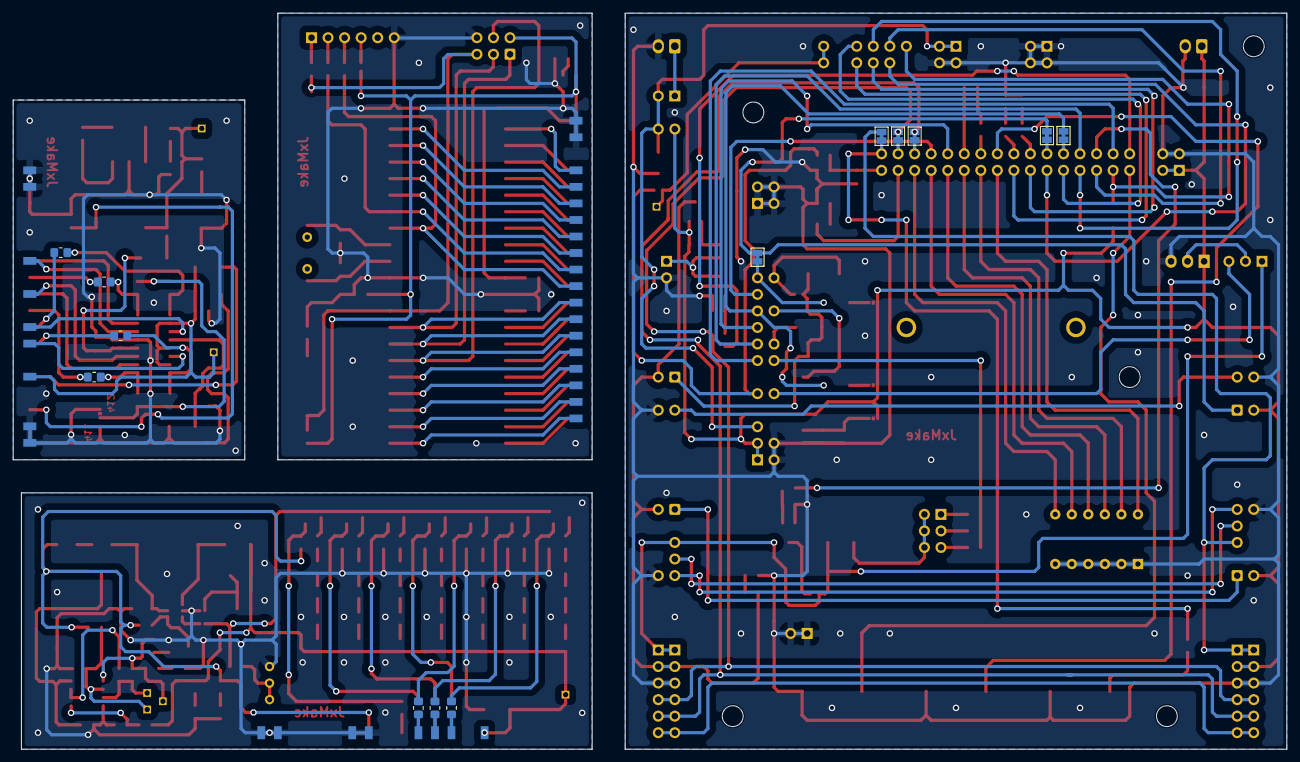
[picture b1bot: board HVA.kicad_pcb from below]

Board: 2 copper layers, 195.6 x 113.0 mm, 227 parts (16 on the bottom side), 218 nets.

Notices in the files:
hardware/JxMake_USB_GPIO_II/KiCad8/High_Voltage_Attachment/HVA.kicad_sch:
This file is part of the JxMake program, see LICENSE file for the license details
Copyright (C) Aloysius Indrayanto
